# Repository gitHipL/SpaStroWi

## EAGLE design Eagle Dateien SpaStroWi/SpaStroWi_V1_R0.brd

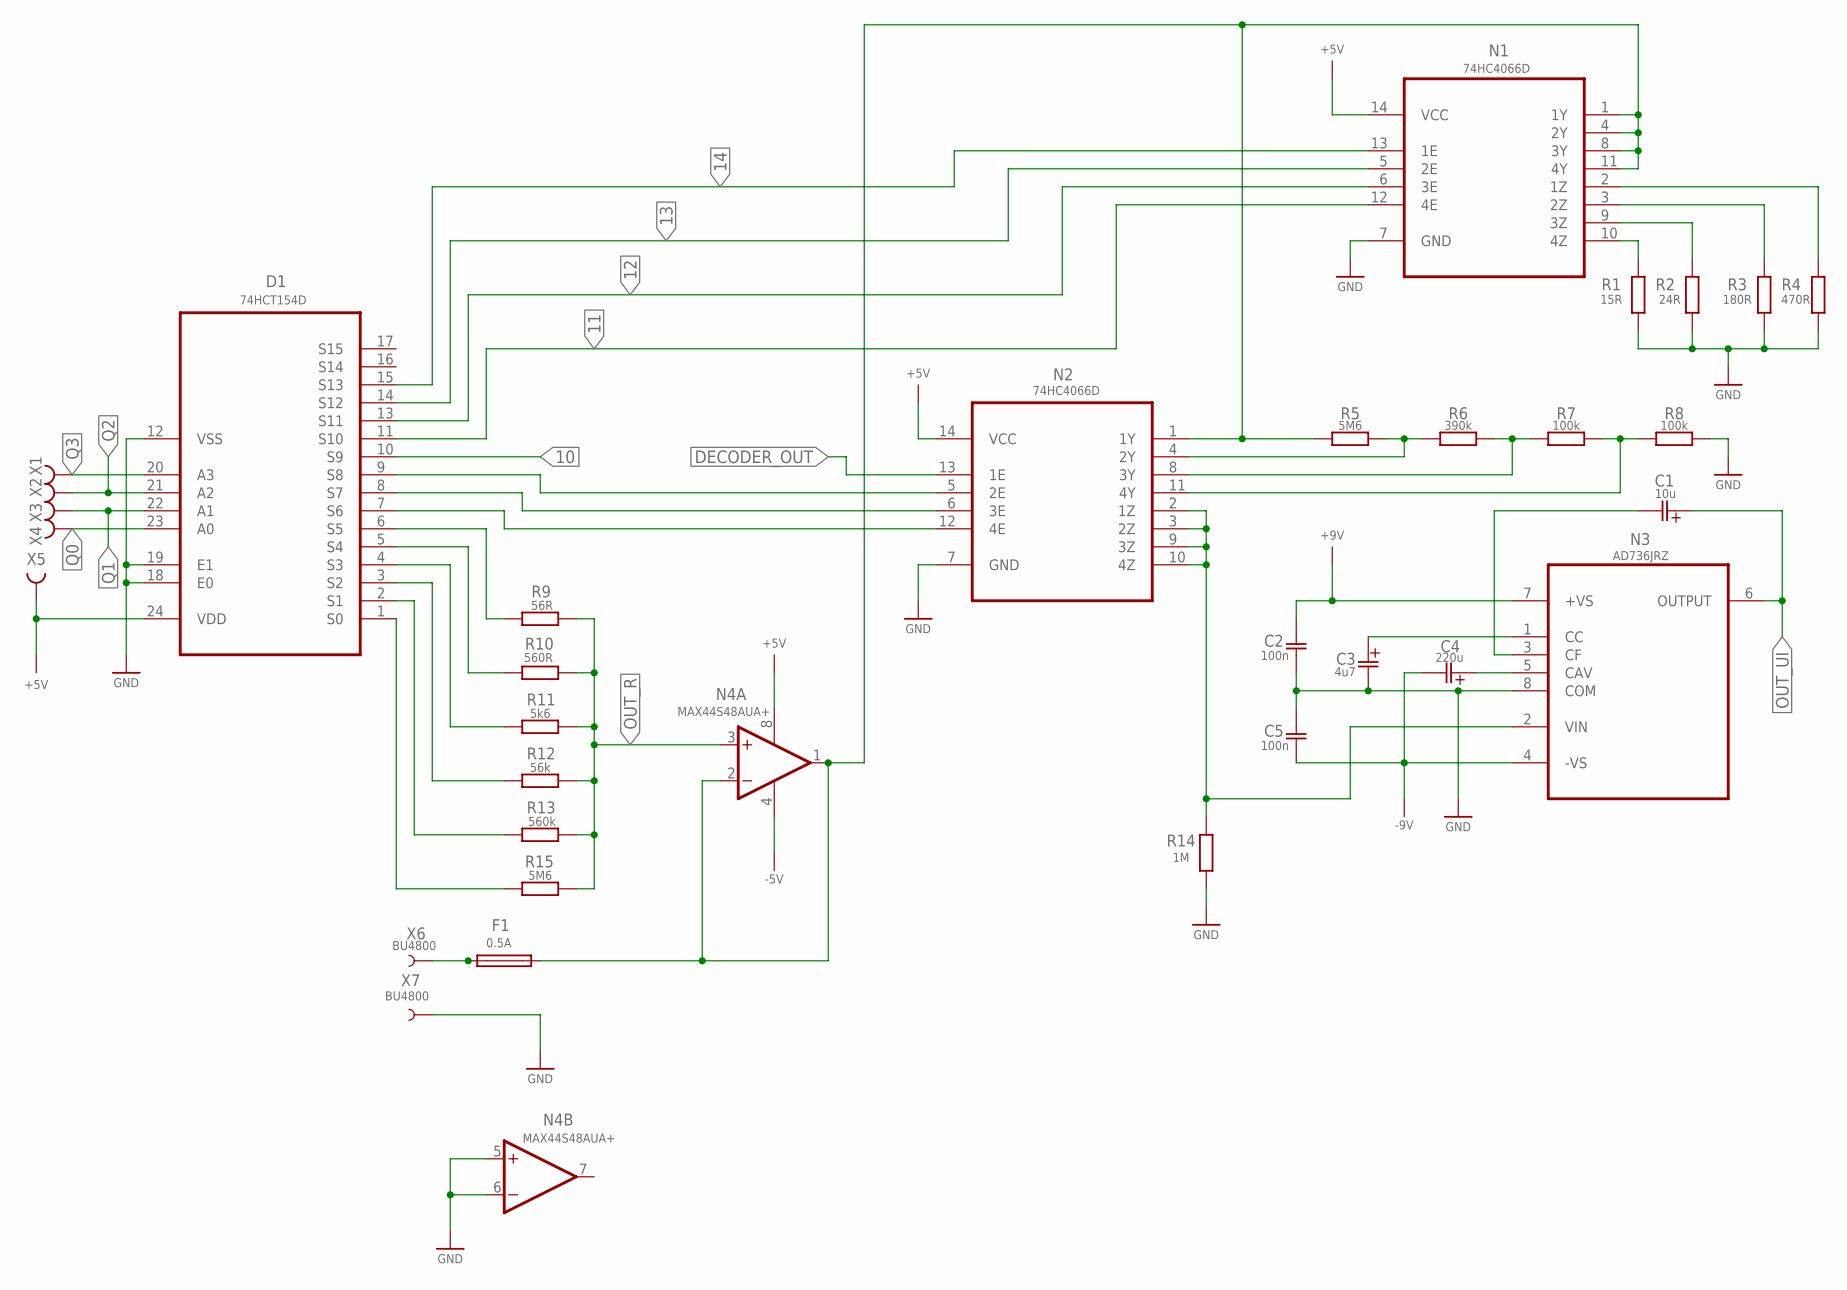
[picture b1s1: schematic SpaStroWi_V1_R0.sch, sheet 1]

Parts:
C1: 10u; 153CLV-0405
C2, C5: 100n; C0805
C3: 4u7; 153CLV-0405
C4: 220u; 153CLV-0405
D1: 74HCT154D; SOIC127P1030X265-24N
F1: 0.5A; 354-0101ZXGY
N1, N2: 74HC4066D; SOIC127P600X175-14N
N3: AD736JRZ; DIP794W45P254L959H508Q8
N4: MAX44S48AUA+; SOP65P490X110-8N
R1: 15R; R2010
R2: 24R; R2512
R3: 180R; R0402
R4: 470R; R0805
R5, R15: 5M6; R0805
R6: 390k; R0805
R7, R8: 100k; R0805
R9: 56R; R0805
R10: 560R; R0805
R11: 5k6; R0805
R12: 56k; R0805
R13: 560k; R0805
R14: 1M; R0805
X1, X2, X3, X4, X5: BUCHSE-V_0.8MM; LSP08
X6, X7: BU4800

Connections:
10: D1.10 (S9); also elsewhere on the board
11: D1.11 (S10), N1.12 (4E); also elsewhere on the board
12: D1.13 (S11), N1.6 (3E); also elsewhere on the board
13: D1.14 (S12), N1.5 (2E); also elsewhere on the board
14: D1.15 (S13), N1.13 (1E); also elsewhere on the board
+5V: D1.24 (VDD), N1.14 (VCC), N2.14 (VCC), N4.8 (VCC+), X5.MP; also elsewhere on the board
+9V: C2.1, N3.7 (+VS); also elsewhere on the board
-5V: N4.4 (VCC-); also elsewhere on the board
-9V: C4.-, C5.2, N3.4 (-VS); also elsewhere on the board
DECODER_OUT: N2.13 (1E); also elsewhere on the board
GND: C2.2, C3.-, C5.1, D1.12 (VSS), D1.18 (E0), D1.19 (E1), N1.7 (GND), N2.7 (GND), N3.8 (COM), N4.5 (NON-INVERTING_INPUT2), N4.6 (INVERTING_INPUT2), R1.1, R2.1, R3.1, R4.1, R8.2, R14.1, X7.P$1; also elsewhere on the board
INPUT: F1.2, N1.1 (1Y), N1.4 (2Y), N1.8 (3Y), N1.11 (4Y), N2.1 (1Y), N4.1 (OUTPUT1), N4.2 (INVERTING_INPUT1), R5.1
unnamed: D1.1 (S0), R15.2
unnamed: D1.2 (S1), R13.2
unnamed: D1.3 (S2), R12.2
unnamed: D1.4 (S3), R11.2
unnamed: D1.5 (S4), R10.2
unnamed: D1.7 (S6), N2.12 (4E)
unnamed: F1.1, X6.P$1
unnamed: N1.10 (4Z), R1.2
unnamed: N1.9 (3Z), R2.2
unnamed: C3.+, N3.1 (CC)
unnamed: N2.8 (3Y), R6.2, R7.1
unnamed: N1.3 (2Z), R3.2
unnamed: N1.2 (1Z), R4.2
unnamed: N2.11 (4Y), R7.2, R8.1
unnamed: N2.4 (2Y), R5.2, R6.1
unnamed: N2.2 (1Z), N2.3 (2Z), N2.9 (3Z), N2.10 (4Z), N3.2 (VIN), R14.2
unnamed: C4.+, N3.5 (CAV)
unnamed: C1.-, N3.3 (CF)
unnamed: D1.6 (S5), R9.2
unnamed: D1.8 (S7), N2.6 (3E)
unnamed: D1.9 (S8), N2.5 (2E)
OUT_R: N4.3 (NON-INVERTING_INPUT1), R9.1, R10.1, R11.1, R12.1, R13.1, R15.1; also elsewhere on the board
OUT_UI: C1.+, N3.6 (OUTPUT); also elsewhere on the board
Q0: D1.23 (A0), X4.MP; also elsewhere on the board
Q1: D1.22 (A1), X3.MP; also elsewhere on the board
Q2: D1.21 (A2), X2.MP; also elsewhere on the board
Q3: D1.20 (A3), X1.MP; also elsewhere on the board

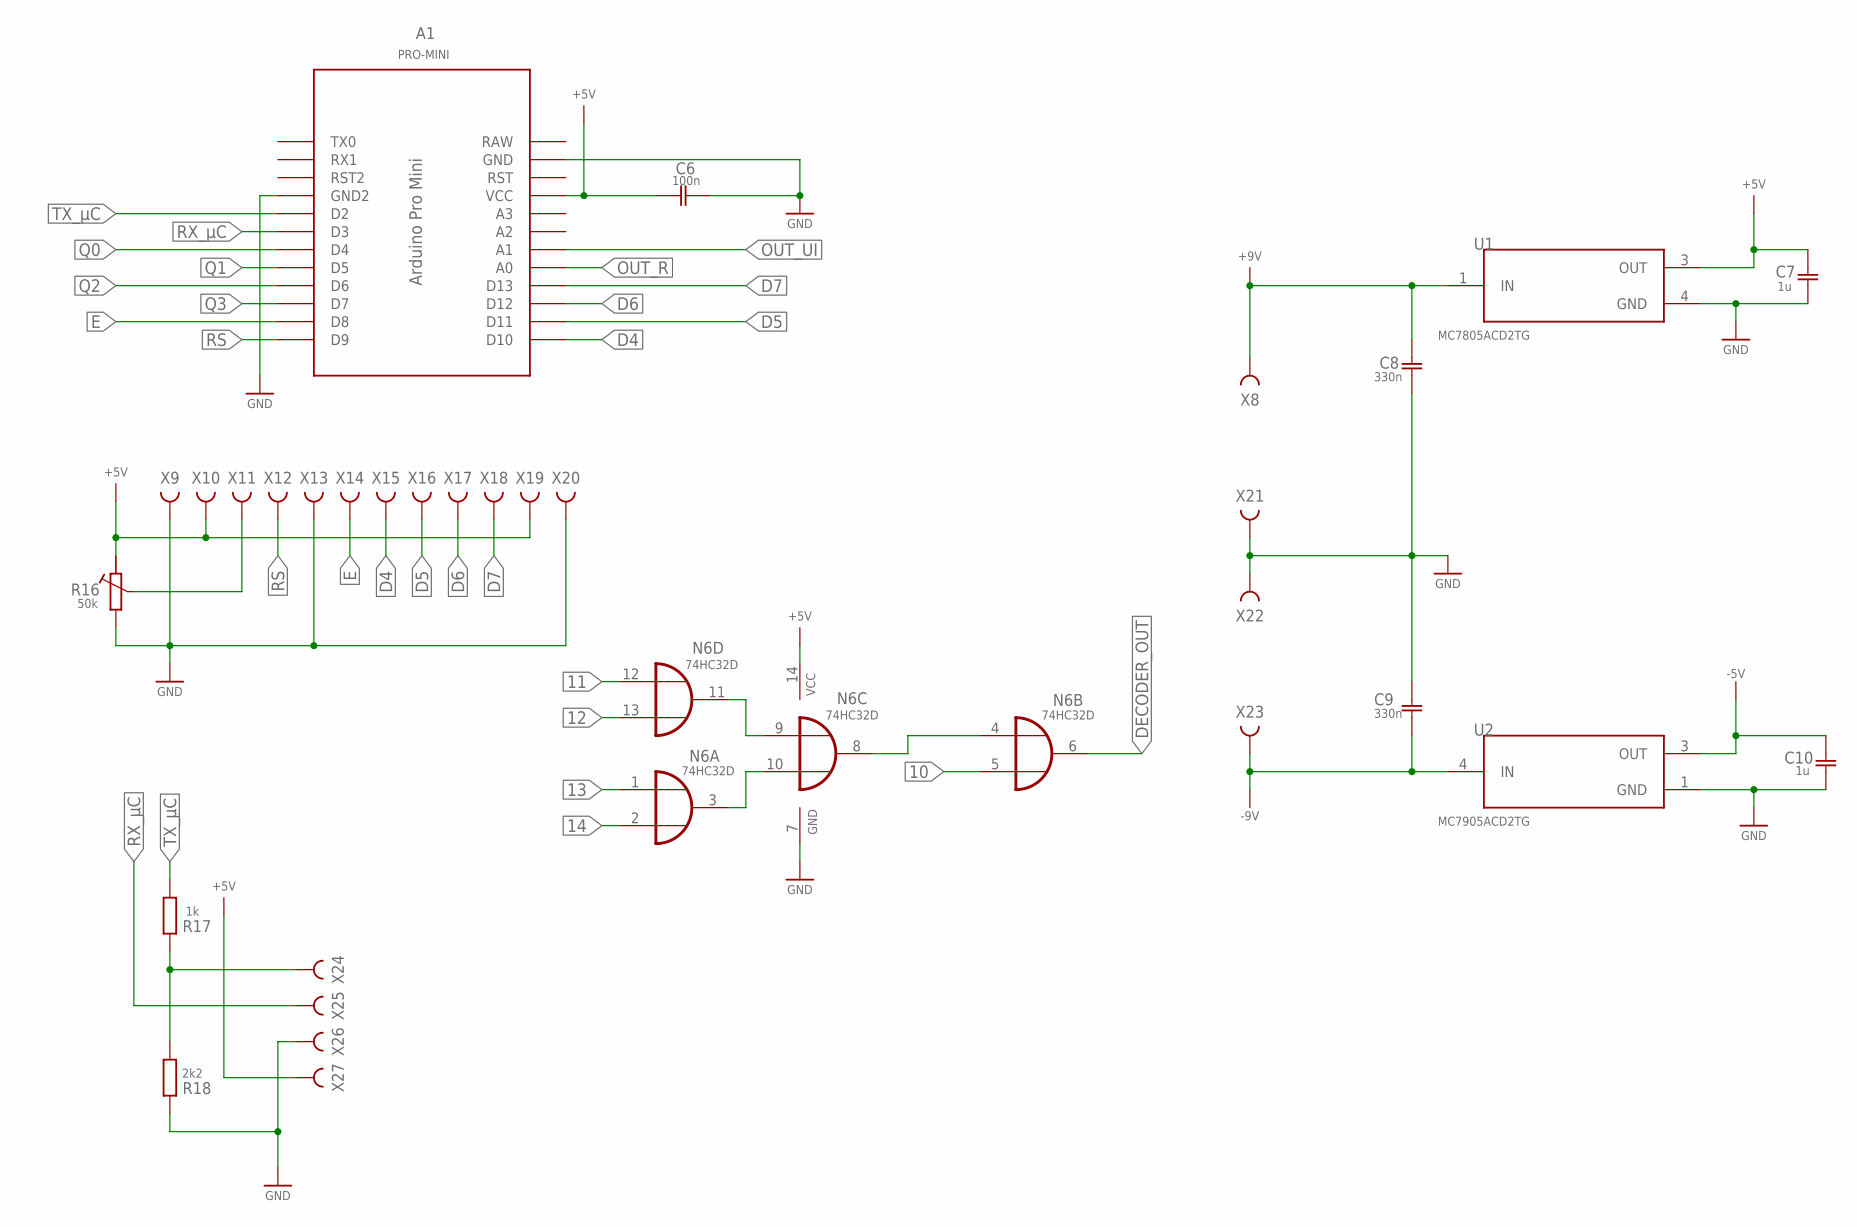
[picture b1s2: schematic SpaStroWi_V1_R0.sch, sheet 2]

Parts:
A1: PRO-MINI
C6: 100n; C0805
C7, C10: 1u; C0805
C8, C9: 330n; C0805
N6: 74HC32D; SO14
R16: 50k; PTV09
R17: 1k; R0805
R18: 2k2; R0805
U1: MC7805ACD2TG; TO254P1420X457-3N
U2: MC7905ACD2TG; TO254P1420X457-3N
X8, X9, X10, X11, X12, X13, X14, X15, X16, X17, X18, X19, X20, X21, X22, X23, X24, X25, X26, X27: BUCHSE-V_0.8MM; LSP08

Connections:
10: N6.5 (I1); also elsewhere on the board
11: N6.12 (I0); also elsewhere on the board
12: N6.13 (I1); also elsewhere on the board
13: N6.1 (I0); also elsewhere on the board
14: N6.2 (I1); also elsewhere on the board
+5V: A1.VCC, C6.1, C7.1, N6.14 (VCC), R16.1 (E), U1.3 (OUT), X10.MP, X19.MP, X27.MP; also elsewhere on the board
+9V: C8.2, U1.1 (IN), X8.MP; also elsewhere on the board
-5V: C10.1, U2.3 (OUT); also elsewhere on the board
-9V: C9.1, U2.4 (IN), X23.MP; also elsewhere on the board
D4: A1.D10, X15.MP
D5: A1.D11, X16.MP
D6: A1.D12, X17.MP
D7: A1.D13, X18.MP
DECODER_OUT: N6.6 (O); also elsewhere on the board
E: A1.D8, X14.MP
GND: A1.GND, A1.GND1 (GND2), C6.2, C7.2, C8.1, C9.2, C10.2, N6.7 (GND), R16.3 (A), R18.2, U1.4 (GND), U2.1 (GND), X9.MP, X13.MP, X20.MP, X21.MP, X22.MP, X26.MP; also elsewhere on the board
unnamed: N6.4 (I0), N6.8 (O)
unnamed: R17.2, R18.1, X24.MP
unnamed: N6.9 (I0), N6.11 (O)
unnamed: N6.3 (O), N6.10 (I1)
unnamed: R16.2 (S), X11.MP
OUT_R: A1.A0; also elsewhere on the board
OUT_UI: A1.A1; also elsewhere on the board
Q0: A1.D4; also elsewhere on the board
Q1: A1.D5; also elsewhere on the board
Q2: A1.D6; also elsewhere on the board
Q3: A1.D7; also elsewhere on the board
RAW: A1.RAW
RS: A1.D9, X12.MP
RX_µC: A1.D3, X25.MP
TX_µC: A1.D2, R17.1

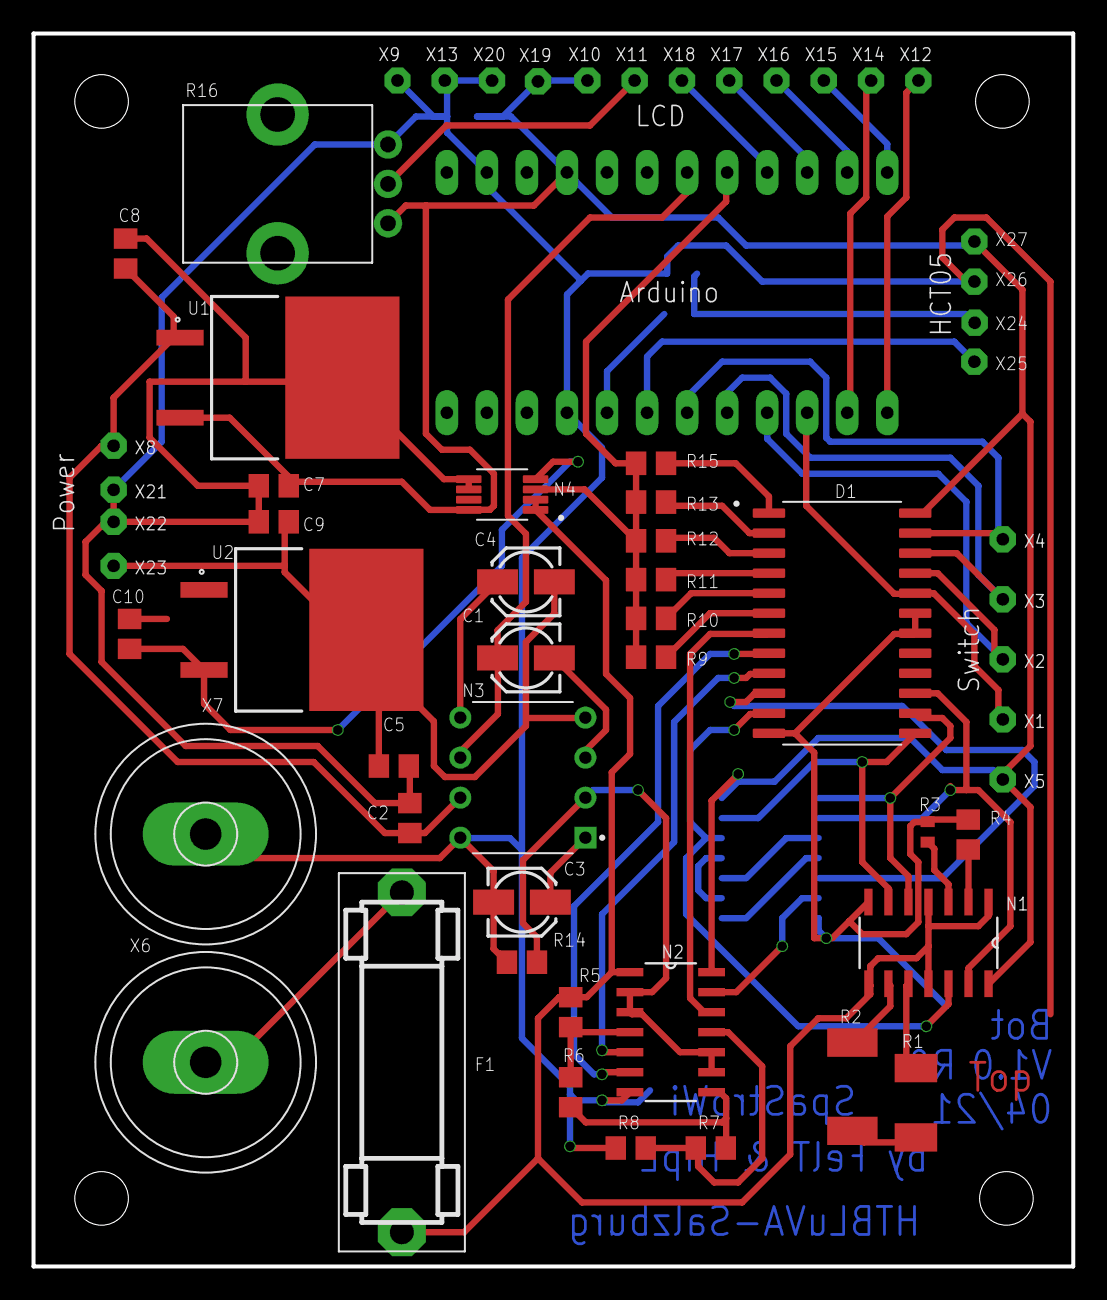
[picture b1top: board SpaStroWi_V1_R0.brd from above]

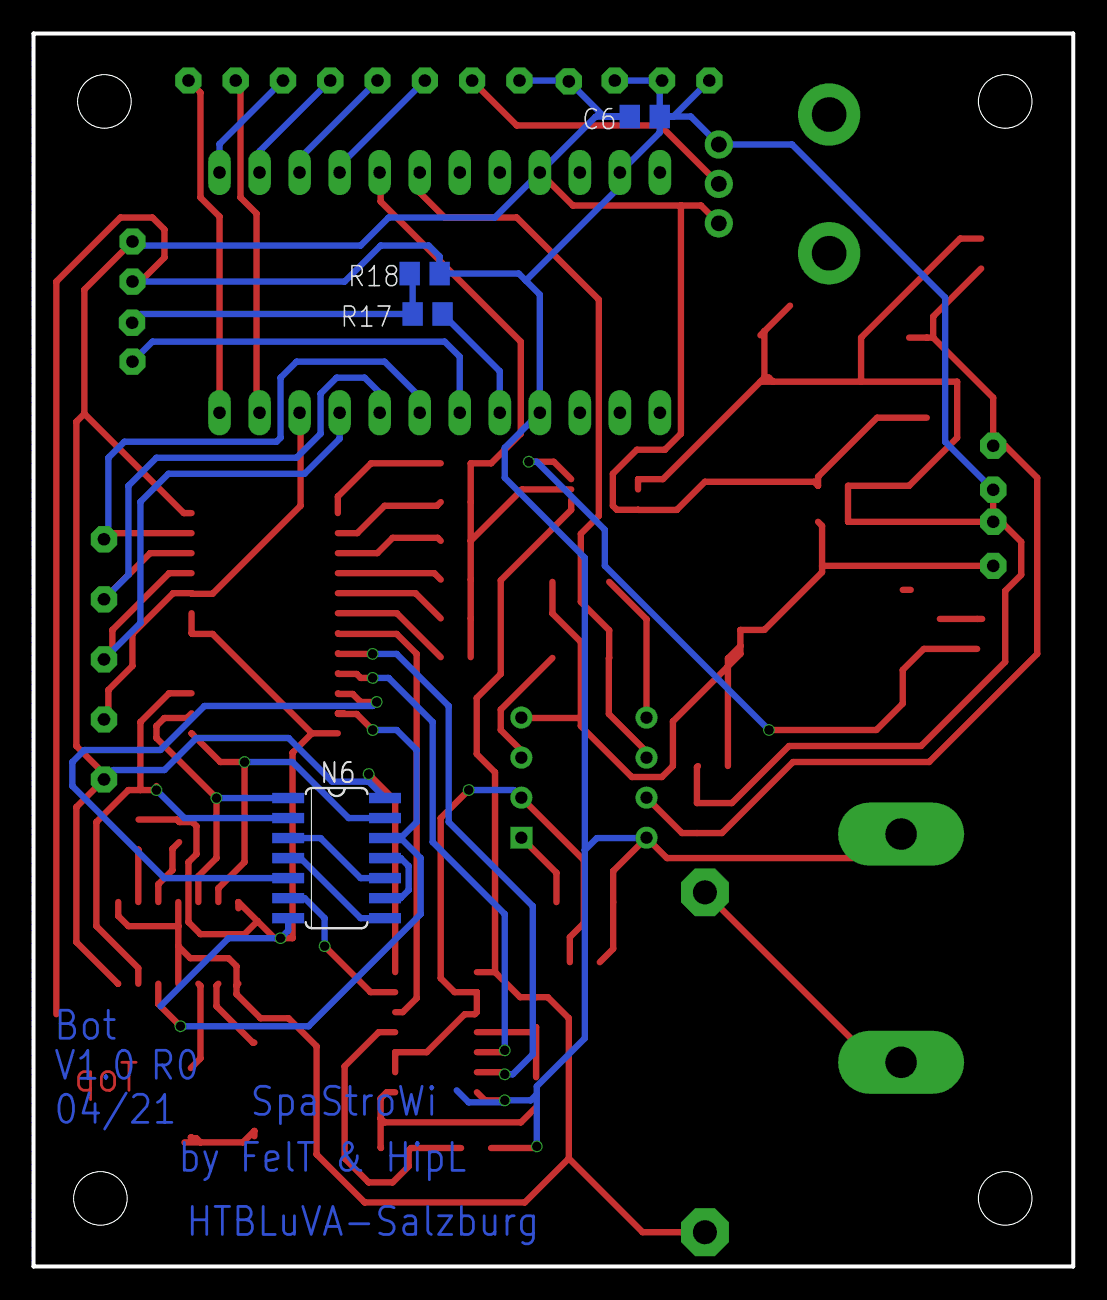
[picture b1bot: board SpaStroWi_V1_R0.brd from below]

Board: 2 copper layers, 66.0 x 78.2 mm, 65 parts (4 on the bottom side), 52 nets.

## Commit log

2021-05-03 Init
2021-05-03 Test commit
